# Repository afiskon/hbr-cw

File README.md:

# HBR/CW

**Update**: The project has some issues with spurious signals. This problem was addressed in [HBR/3B](https://github.com/afiskon/hbr-3b) and [HBR/8B](https://github.com/afiskon/hbr-8b).

All HF bands QRP CW transceiver

* Covers 80, 40, 30, 20, 17, 15, 12 and 10 meter bands
* IF-derived AGC
* Supports RIT, XIT and SHIFT
* 10-30 WPM Elekey-B type keyer + straight key mode
* Keyer settings are saved in EEPROM
* 5W class C power amplifier
* 9-pole low-pass filters
* HIGH SWR indicator
* Open-source firmware and hardware

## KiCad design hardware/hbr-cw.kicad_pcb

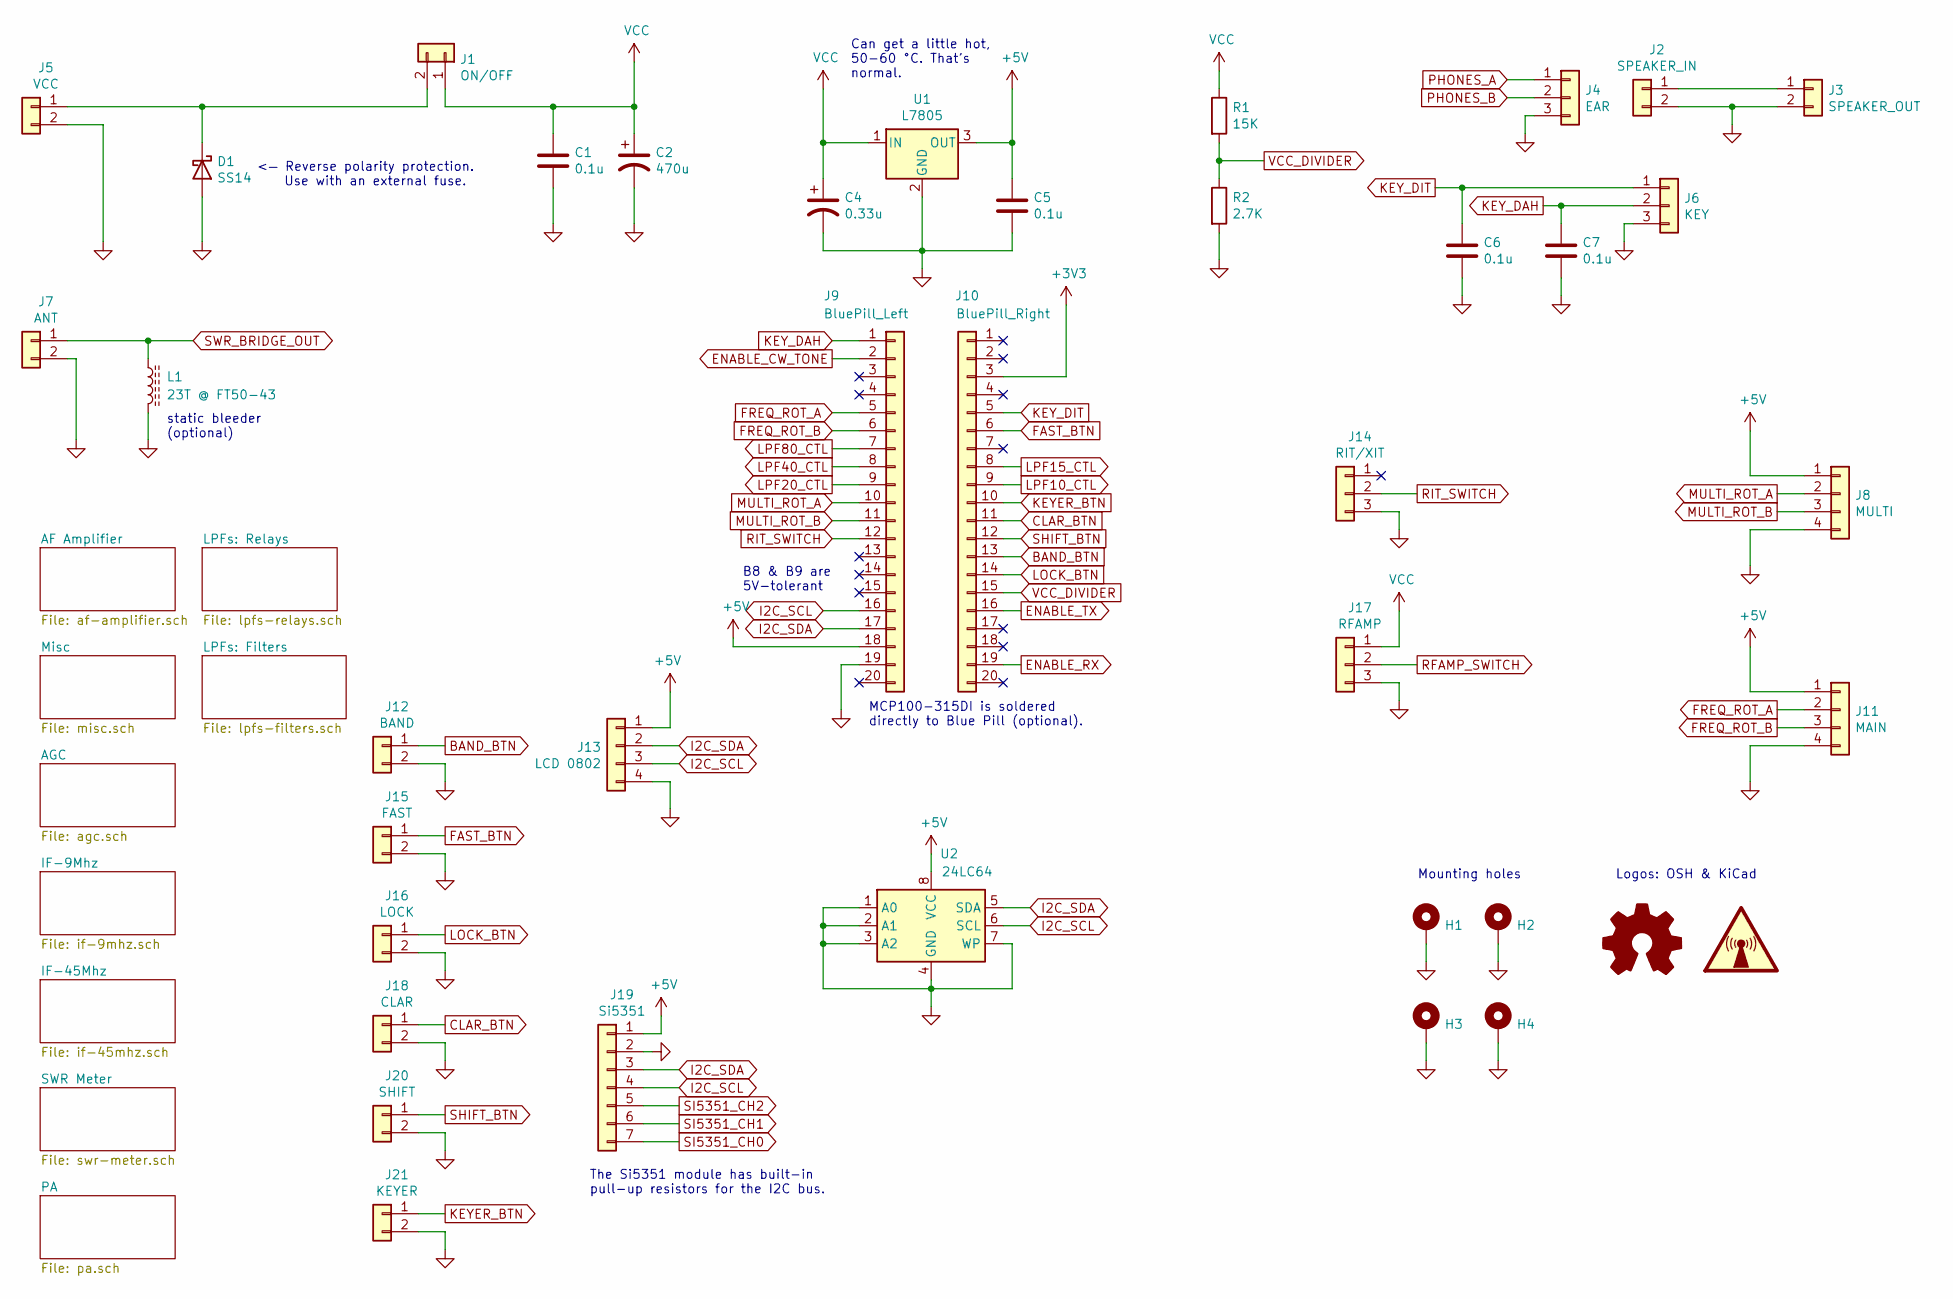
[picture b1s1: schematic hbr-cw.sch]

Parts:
C1, C5, C6, C7: 0.1u; C_0805_2012Metric_Pad1.15x1.40mm_HandSolder
C2: 470u; CP_Elec_10x10.5
C4: 0.33u; C_Radial_D5.0mm_H5.0mm_P2.00mm
D1: SS14; D_SMA_Handsoldering
H1, H2, H3, H4: MH; MountingHole_3.2mm_M3_Pad_Via
J1: ON/OFF; PinHeader_1x02_P2.54mm_Vertical
J2: SPEAKER_IN; PinHeader_1x02_P2.54mm_Vertical
J3: SPEAKER_OUT; PinHeader_1x02_P2.54mm_Vertical
J4: EAR; PinSocket_1x03_P2.54mm_Vertical
J5: VCC; PinHeader_1x02_P2.54mm_Vertical
J6: KEY; PinSocket_1x03_P2.54mm_Vertical
J7: ANT; PinHeader_1x02_P2.54mm_Vertical
J8: MULTI; PinHeader_1x04_P2.54mm_Vertical
J9: BluePill_Left; PinSocket_1x20_P2.54mm_Vertical
J10: BluePill_Right; PinSocket_1x20_P2.54mm_Vertical
J11: MAIN; PinHeader_1x04_P2.54mm_Vertical
J12: BAND; PinHeader_1x02_P2.54mm_Vertical
J13: LCD 0802; PinHeader_1x04_P2.54mm_Vertical
J14: RIT/XIT; PinSocket_1x03_P2.54mm_Vertical
J15: FAST; PinHeader_1x02_P2.54mm_Vertical
J16: LOCK; PinHeader_1x02_P2.54mm_Vertical
J17: RFAMP; PinSocket_1x03_P2.54mm_Vertical
J18: CLAR; PinHeader_1x02_P2.54mm_Vertical
J19: Si5351; PinHeader_1x07_P2.54mm_Vertical
J20: SHIFT; PinHeader_1x02_P2.54mm_Vertical
J21: KEYER; PinHeader_1x02_P2.54mm_Vertical
L1: 23T @ FT50-43; L_Toroid_Vertical_L13.0mm_W6.5mm_P5.60mm
R1: 15K; R_0805_2012Metric_Pad1.15x1.40mm_HandSolder
R2: 2.7K; R_0805_2012Metric_Pad1.15x1.40mm_HandSolder
SYM1: Logo_Open_Hardware_Small; OSHW-Logo2_9.8x8mm_SilkScreen
SYM2: SYM_Radio_Waves_Large; KiCad-Logo_5mm_SilkScreen
U1: L7805; TO-263-2
U2: 24LC64; SO-8_5.3x6.2mm_P1.27mm

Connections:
+3V3: J10.3
+5V: C5.1, J8.1, J9.18, J11.1, J13.1, J19.1, U1.3 (OUT), U2.8 (VCC); also elsewhere on the board
BAND_BTN: J10.13, J12.1
CLAR_BTN: J10.11, J18.1
ENABLE_CW_TONE: J9.2; also elsewhere on the board
ENABLE_RX: J10.19; also elsewhere on the board
ENABLE_TX: J10.16; also elsewhere on the board
FAST_BTN: J10.6, J15.1
FREQ_ROT_A: J9.5, J11.2
FREQ_ROT_B: J9.6, J11.3
GND: C1.2, C2.2, C4.2, C5.2, C6.2, C7.2, D1.2 (A), H1.1, H2.1, H3.1, H4.1, J2.2, J3.2, J4.3, J5.2, J6.3, J7.2, J8.4, J9.19, J11.4, J12.2, J13.4, J14.3, J15.2, J16.2, J17.3, J18.2, J19.2, J20.2, J21.2, L1.2, R2.2, U1.2 (GND), U2.1 (A0), U2.2 (A1), U2.3 (A2), U2.4 (GND), U2.7 (WP); also elsewhere on the board
I2C_SCL: J9.16, J13.3, J19.4, U2.6 (SCL); also elsewhere on the board
I2C_SDA: J9.17, J13.2, J19.3, U2.5 (SDA); also elsewhere on the board
KEYER_BTN: J10.10, J21.1
KEY_DAH: C7.1, J6.2, J9.1
KEY_DIT: C6.1, J6.1, J10.5
LOCK_BTN: J10.14, J16.1
LPF10_CTL: J10.9; also elsewhere on the board
LPF15_CTL: J10.8; also elsewhere on the board
LPF20_CTL: J9.9; also elsewhere on the board
LPF40_CTL: J9.8; also elsewhere on the board
LPF80_CTL: J9.7; also elsewhere on the board
MULTI_ROT_A: J8.2, J9.10
MULTI_ROT_B: J8.3, J9.11
unnamed: D1.1 (K), J1.2, J5.1
unnamed: J2.1, J3.1
PHONES_A: J4.1; also elsewhere on the board
PHONES_B: J4.2; also elsewhere on the board
RFAMP_SWITCH: J17.2; also elsewhere on the board
RIT_SWITCH: J9.12, J14.2
SHIFT_BTN: J10.12, J20.1
SI5351_CH0: J19.7; also elsewhere on the board
SI5351_CH1: J19.6; also elsewhere on the board
SI5351_CH2: J19.5; also elsewhere on the board
SWR_BRIDGE_OUT: J7.1, L1.1; also elsewhere on the board
VCC: C1.1, C2.1, C4.1, J1.1, J17.1, R1.1, U1.1 (IN); also elsewhere on the board
VCC_DIVIDER: J10.15, R1.2, R2.1

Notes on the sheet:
<— Reverse polarity protection. Use with an external fuse.
The Si5351 module has built-in pull-up resistors for the I2C bus.
static bleeder (optional)
B8 & B9 are 5V-tolerant
MCP100-315DI is soldered directly to Blue Pill (optional).
Mounting holes
Logos: OSH & KiCad
Can get a little hot, 50-60 °C. That’s normal.

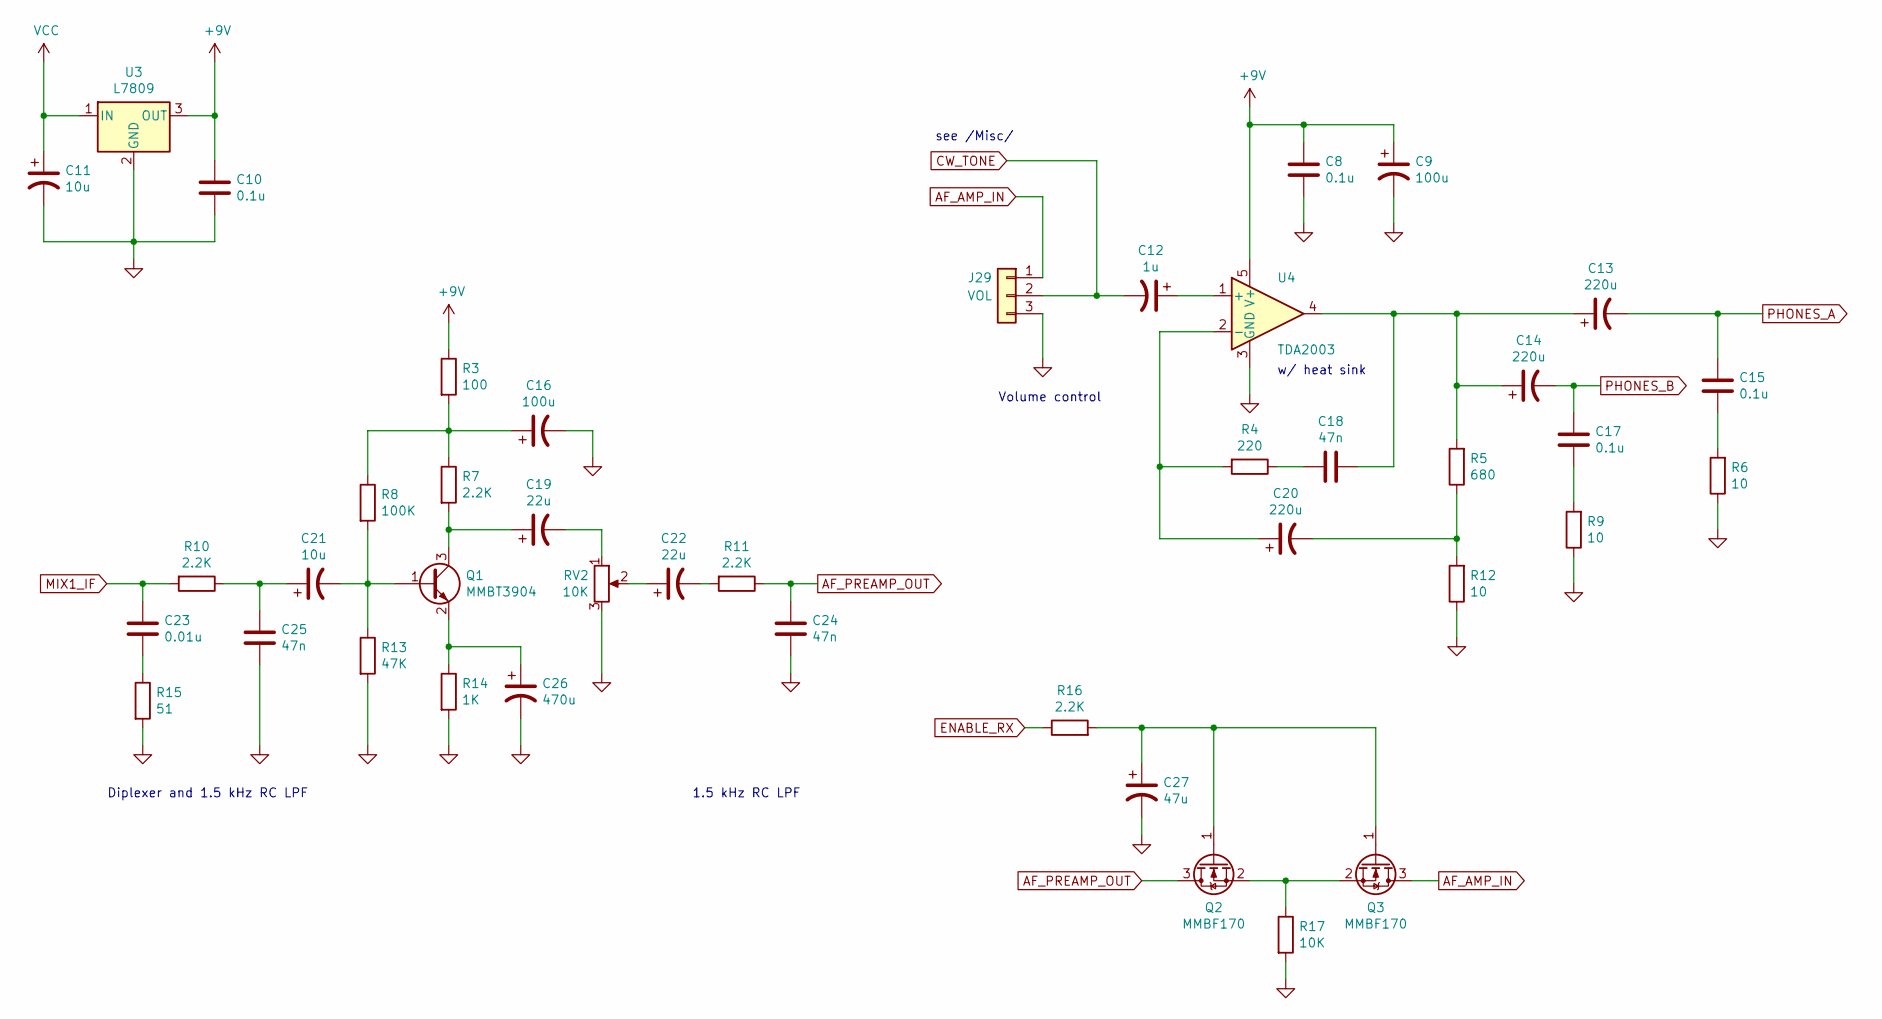
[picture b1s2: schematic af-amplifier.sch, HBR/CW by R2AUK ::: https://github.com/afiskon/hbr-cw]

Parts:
C8, C10, C15, C17: 0.1u; C_0805_2012Metric_Pad1.15x1.40mm_HandSolder
C9, C16: 100u; CP_Elec_6.3x7.7
C11, C21: 10u; CP_Elec_4x5.4
C12: 1u; CP_Elec_4x5.4
C13, C14, C20: 220u; CP_Elec_8x10.5
C18, C24, C25: 47n; C_0805_2012Metric_Pad1.15x1.40mm_HandSolder
C19, C22: 22u; CP_Elec_5x5.4
C23: 0.01u; C_0805_2012Metric_Pad1.15x1.40mm_HandSolder
C26: 470u; CP_Elec_10x10.5
C27: 47u; CP_Elec_6.3x5.8
J29: VOL; PinSocket_1x03_P2.54mm_Vertical
Q1: MMBT3904; SOT-23
Q2, Q3: MMBF170; SOT-23
R3: 100; R_0805_2012Metric_Pad1.15x1.40mm_HandSolder
R4: 220; R_0805_2012Metric_Pad1.15x1.40mm_HandSolder
R5: 680; R_0805_2012Metric_Pad1.15x1.40mm_HandSolder
R6, R9, R12: 10; R_0805_2012Metric_Pad1.15x1.40mm_HandSolder
R7, R10, R11, R16: 2.2K; R_0805_2012Metric_Pad1.15x1.40mm_HandSolder
R8: 100K; R_0805_2012Metric_Pad1.15x1.40mm_HandSolder
R13: 47K; R_0805_2012Metric_Pad1.15x1.40mm_HandSolder
R14: 1K; R_0805_2012Metric_Pad1.15x1.40mm_HandSolder
R15: 51; R_0805_2012Metric_Pad1.15x1.40mm_HandSolder
R17: 10K; R_0805_2012Metric_Pad1.15x1.40mm_HandSolder
RV2: 10K; Potentiometer_Bourns_3296W_Vertical
U3: L7809; TO-263-2
U4: TDA2003; TO-220-5_P3.4x3.7mm_StaggerOdd_Lead3.8mm_Vertical

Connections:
+9V: C8.1, C9.1, C10.1, R3.1, U3.3 (OUT), U4.5 (V+); also elsewhere on the board
AF_AMP_IN: J29.1, Q3.3 (D)
AF_PREAMP_OUT: C24.1, Q2.3 (D), R11.1
CW_TONE: C12.2, J29.2; also elsewhere on the board
ENABLE_RX: R16.1; also elsewhere on the board
GND: C8.2, C9.2, C10.2, C11.2, C16.2, C24.2, C25.2, C26.2, C27.2, J29.3, R6.1, R9.1, R12.1, R13.2, R14.2, R15.2, R17.2, RV2.3, U3.2 (GND), U4.3 (GND); also elsewhere on the board
MIX1_IF: C23.1, R10.2; also elsewhere on the board
unnamed: C12.1, U4.1 (+)
unnamed: C13.1, C14.1, C18.1, R5.2, U4.4
unnamed: C15.2, R6.2
unnamed: C16.1, R3.2, R7.1, R8.1
unnamed: C17.2, R9.2
unnamed: C18.2, R4.1
unnamed: C19.1, Q1.3 (C), R7.2
unnamed: C19.2, RV2.1
unnamed: C20.1, R4.2, U4.2 (-)
unnamed: C20.2, R5.1, R12.2
unnamed: C21.1, C25.1, R10.1
unnamed: C21.2, Q1.1 (B), R8.2, R13.1
unnamed: C22.1, RV2.2
unnamed: C22.2, R11.2
unnamed: C23.2, R15.1
unnamed: C26.1, Q1.2 (E), R14.1
unnamed: C27.1, Q2.1 (G), Q3.1 (G), R16.2
unnamed: Q2.2 (S), Q3.2 (S), R17.1
PHONES_A: C13.2, C15.1; also elsewhere on the board
PHONES_B: C14.2, C17.1; also elsewhere on the board
VCC: C11.1, U3.1 (IN); also elsewhere on the board

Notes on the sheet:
Volume control
w/ heat sink
see /Misc/
Diplexer and 1.5 kHz RC LPF
1.5 kHz RC LPF

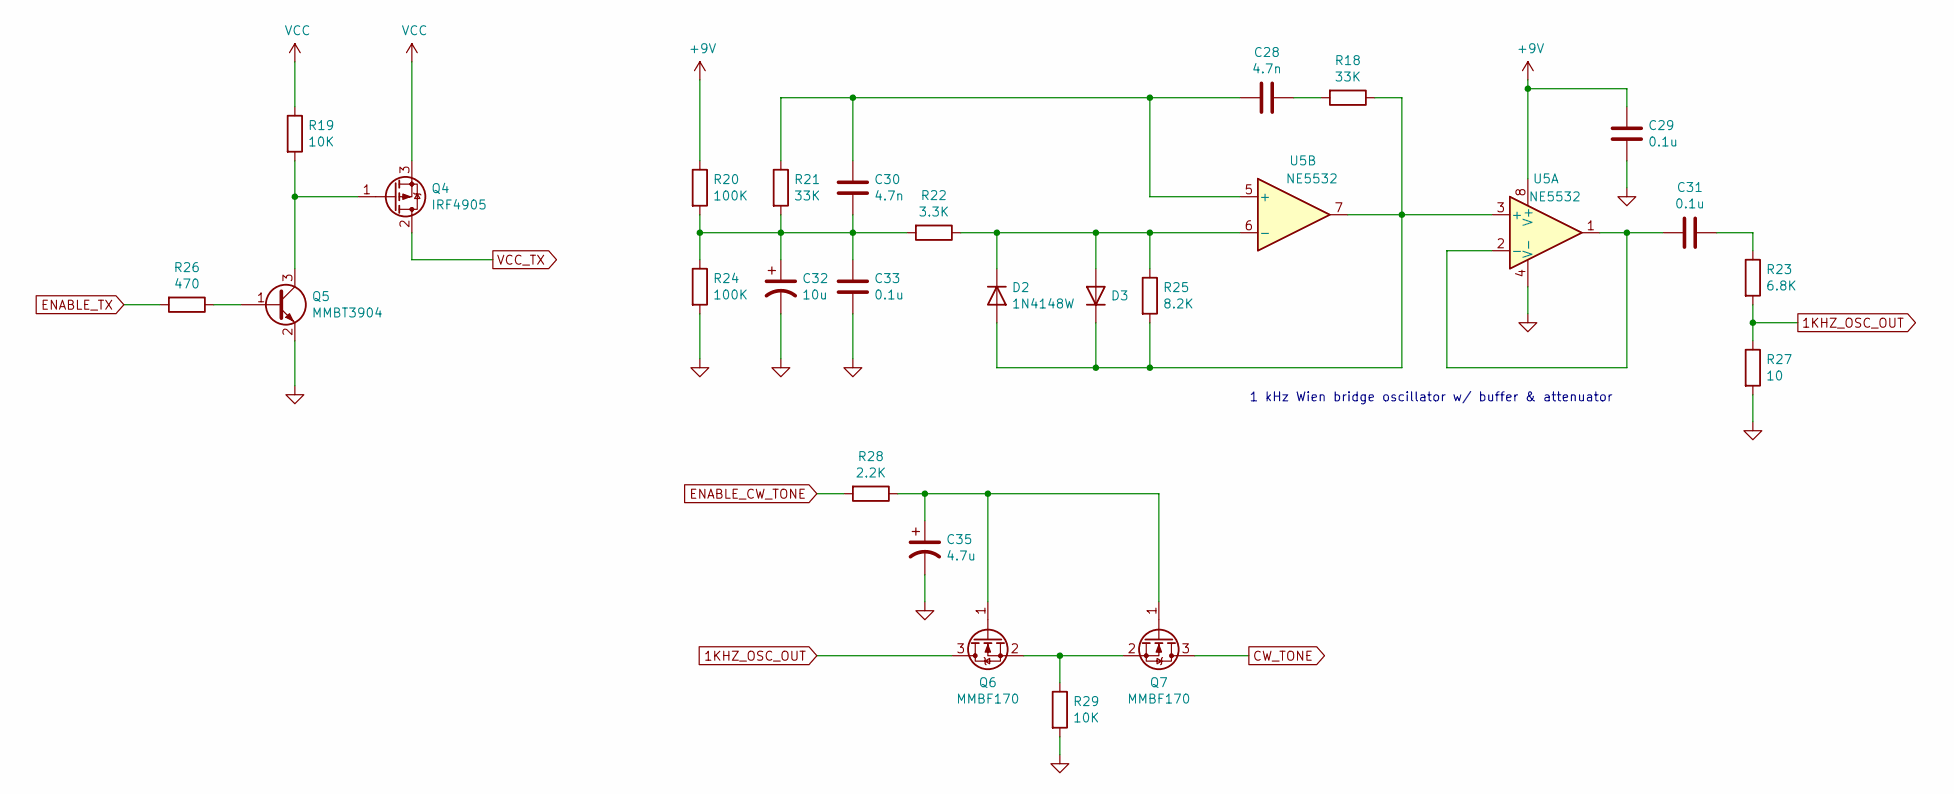
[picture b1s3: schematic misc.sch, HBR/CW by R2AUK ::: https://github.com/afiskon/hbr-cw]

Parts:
C28, C30: 4.7n; C_0805_2012Metric_Pad1.15x1.40mm_HandSolder
C29, C31, C33: 0.1u; C_0805_2012Metric_Pad1.15x1.40mm_HandSolder
C32: 10u; CP_Elec_4x5.4
C35: 4.7u; CP_Elec_4x5.4
D2, D3: 1N4148W; D_SOD-123
Q4: IRF4905; TO-220-3_Vertical
Q5: MMBT3904; SOT-23
Q6, Q7: MMBF170; SOT-23
R18, R21: 33K; R_0805_2012Metric_Pad1.15x1.40mm_HandSolder
R19, R29: 10K; R_0805_2012Metric_Pad1.15x1.40mm_HandSolder
R20, R24: 100K; R_0805_2012Metric_Pad1.15x1.40mm_HandSolder
R22: 3.3K; R_0805_2012Metric_Pad1.15x1.40mm_HandSolder
R23: 6.8K; R_0805_2012Metric_Pad1.15x1.40mm_HandSolder
R25: 8.2K; R_0805_2012Metric_Pad1.15x1.40mm_HandSolder
R26: 470; R_0805_2012Metric_Pad1.15x1.40mm_HandSolder
R27: 10; R_0805_2012Metric_Pad1.15x1.40mm_HandSolder
R28: 2.2K; R_0805_2012Metric_Pad1.15x1.40mm_HandSolder
U5: NE5532; SOIC-8_5.23x5.23mm_P1.27mm

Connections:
1KHZ_OSC_OUT: Q6.3 (D), R23.2, R27.1
+9V: C29.2, R20.1, U5.8 (V+); also elsewhere on the board
CW_TONE: Q7.3 (D); also elsewhere on the board
ENABLE_CW_TONE: R28.2; also elsewhere on the board
ENABLE_TX: R26.2; also elsewhere on the board
GND: C29.1, C32.2, C33.2, C35.2, Q5.2 (E), R24.2, R27.2, R29.2, U5.4 (V-); also elsewhere on the board
unnamed: C28.1, R18.2
unnamed: C28.2, C30.1, R21.1, U5.5 (+)
unnamed: C30.2, C32.1, C33.1, R20.2, R21.2, R22.2, R24.1
unnamed: C31.1, R23.1
unnamed: C31.2, U5.1, U5.2 (-)
unnamed: C35.1, Q6.1 (G), Q7.1 (G), R28.1
unnamed: D2.1 (K), D3.2 (A), R22.1, R25.1, U5.6 (-)
unnamed: D2.2 (A), D3.1 (K), R18.1, R25.2, U5.3 (+), U5.7
unnamed: Q4.1 (G), Q5.3 (C), R19.2
unnamed: Q5.1 (B), R26.1
unnamed: Q6.2 (S), Q7.2 (S), R29.1
VCC: Q4.3 (S), R19.1; also elsewhere on the board
VCC_TX: Q4.2 (D); also elsewhere on the board

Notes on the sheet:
1 kHz Wien bridge oscillator w/ buffer & attenuator

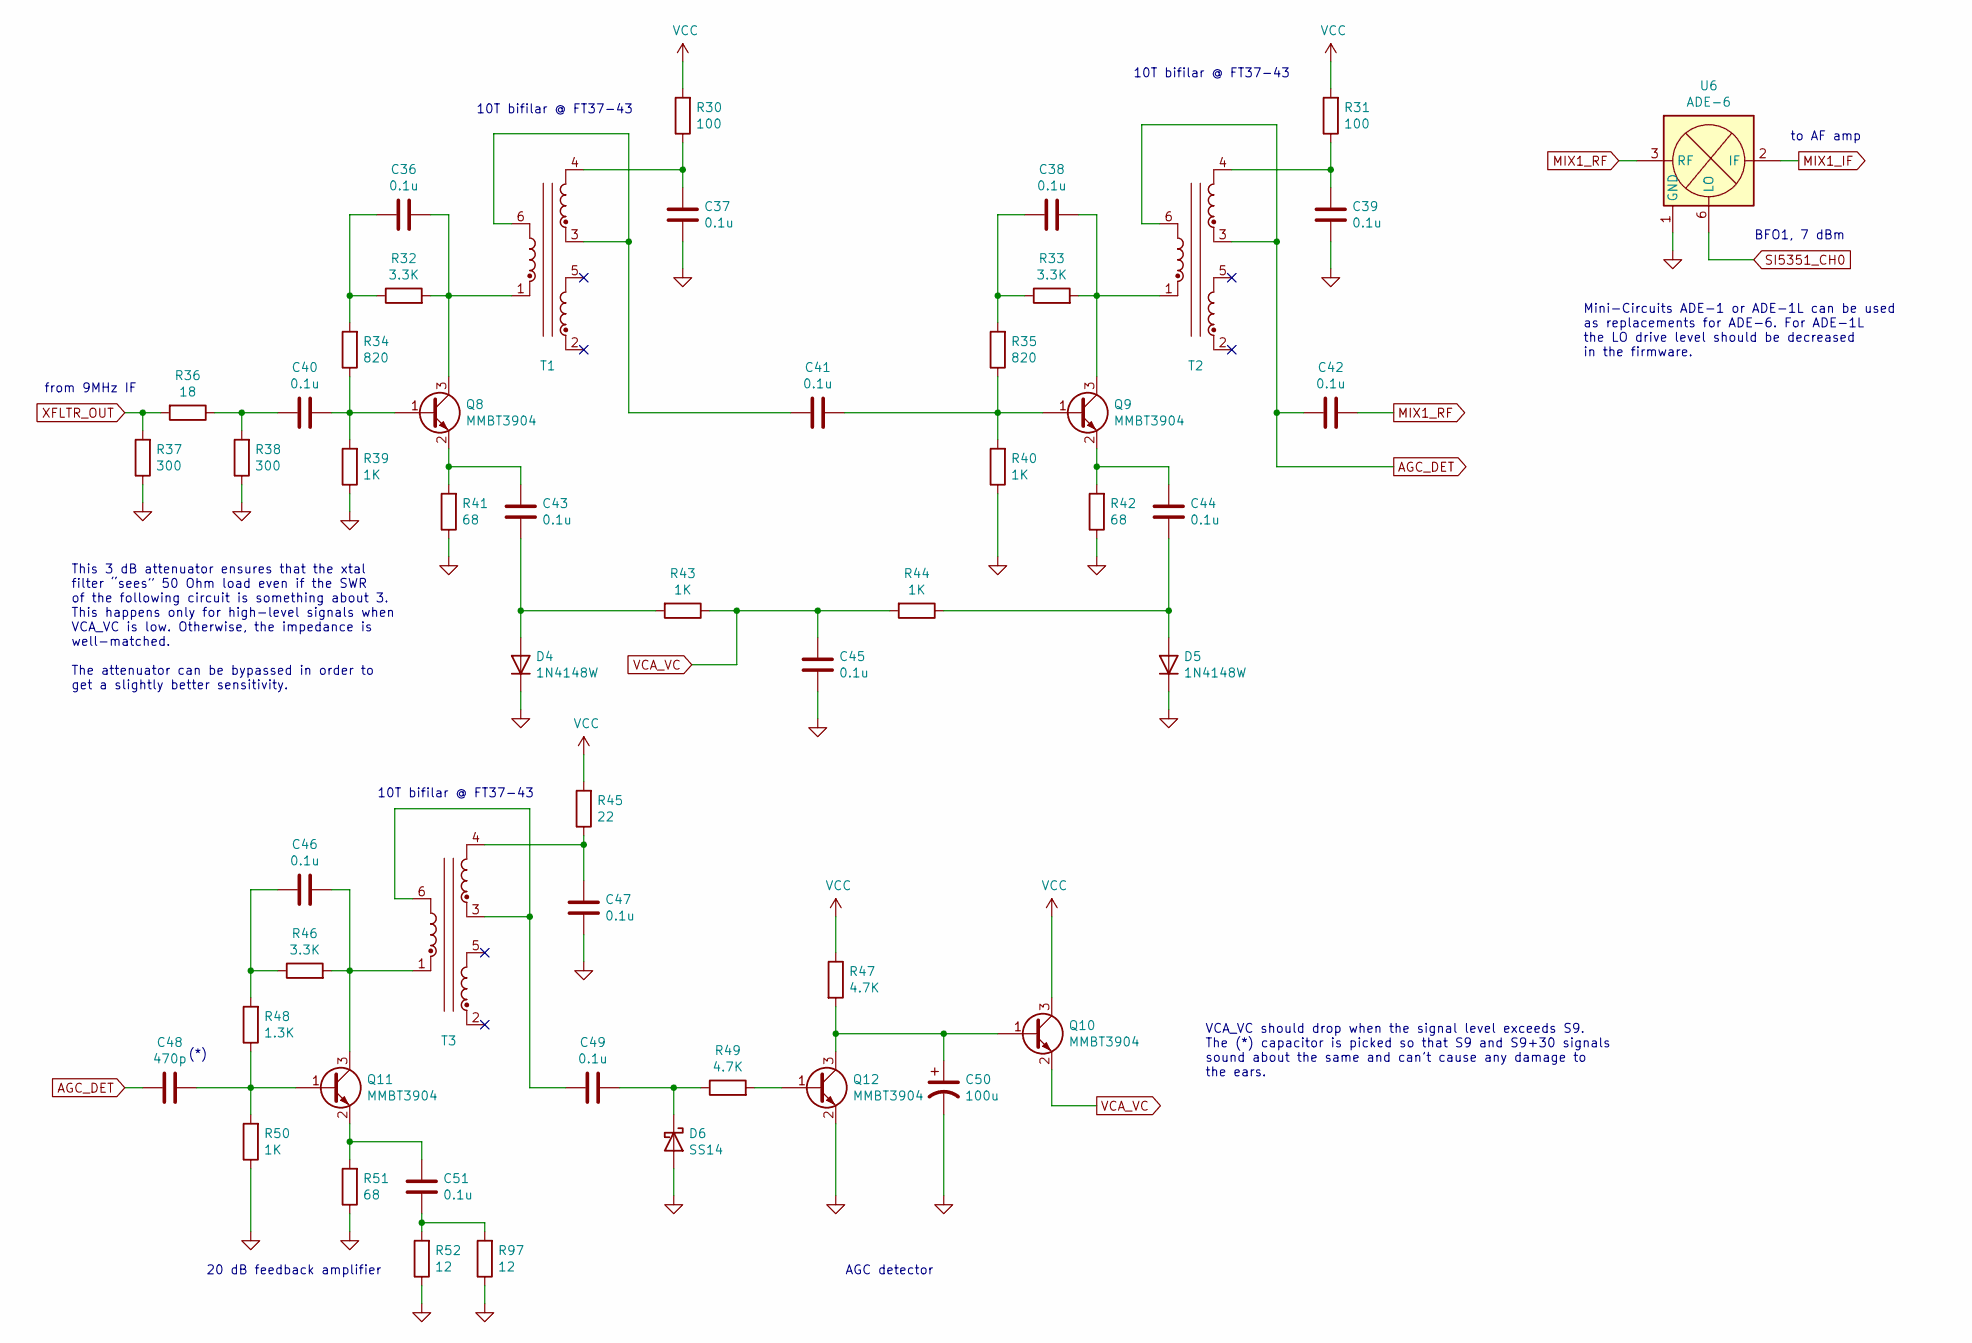
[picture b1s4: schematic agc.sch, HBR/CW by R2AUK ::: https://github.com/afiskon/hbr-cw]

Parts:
C36, C37, C38, C39, C40, C41, C42, C43, C44, C45, C46, C47, C49, C51: 0.1u; C_0805_2012Metric_Pad1.15x1.40mm_HandSolder
C48: 470p; C_0805_2012Metric_Pad1.15x1.40mm_HandSolder
C50: 100u; CP_Elec_6.3x7.7
D4, D5: 1N4148W; D_SOD-123
D6: SS14; D_SMA_Handsoldering
Q8, Q9, Q10, Q11, Q12: MMBT3904; SOT-23
R30, R31: 100; R_0805_2012Metric_Pad1.15x1.40mm_HandSolder
R32, R33, R46: 3.3K; R_0805_2012Metric_Pad1.15x1.40mm_HandSolder
R34, R35: 820; R_0805_2012Metric_Pad1.15x1.40mm_HandSolder
R36: 18; R_0805_2012Metric_Pad1.15x1.40mm_HandSolder
R37, R38: 300; R_0805_2012Metric_Pad1.15x1.40mm_HandSolder
R39, R40, R43, R44, R50: 1K; R_0805_2012Metric_Pad1.15x1.40mm_HandSolder
R41, R42, R51: 68; R_0805_2012Metric_Pad1.15x1.40mm_HandSolder
R45: 22; R_0805_2012Metric_Pad1.15x1.40mm_HandSolder
R47, R49: 4.7K; R_0805_2012Metric_Pad1.15x1.40mm_HandSolder
R48: 1.3K; R_0805_2012Metric_Pad1.15x1.40mm_HandSolder
R52, R97: 12; R_0805_2012Metric_Pad1.15x1.40mm_HandSolder
T1, T2, T3: FT37-43; DIP-6_W7.62mm
U6: ADE-6; Mini-Circuits_CD542_LandPatternPL-052

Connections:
AGC_DET: C42.2, C48.2, T2.3, T2.6
GND: C37.1, C39.1, C45.1, C47.1, C50.2, D4.1 (K), D5.1 (K), D6.2 (A), Q12.2 (E), R37.1, R38.1, R39.1, R40.1, R41.1, R42.1, R50.1, R51.1, R52.1, R97.1, U6.1 (GND), U6.4 (GND), U6.5 (GND); also elsewhere on the board
MIX1_IF: U6.2 (IF); also elsewhere on the board
MIX1_RF: C42.1, U6.3 (RF)
unnamed: C36.1, Q8.3 (C), R32.2, T1.1
unnamed: C36.2, R32.1, R34.2
unnamed: C37.2, R30.1, T1.4
unnamed: C38.1, Q9.3 (C), R33.2, T2.1
unnamed: C38.2, R33.1, R35.2
unnamed: C39.2, R31.1, T2.4
unnamed: C40.1, Q8.1 (B), R34.1, R39.2
unnamed: C40.2, R36.1, R38.2
unnamed: C41.1, Q9.1 (B), R35.1, R40.2
unnamed: C41.2, T1.3, T1.6
unnamed: C43.1, D4.2 (A), R43.2
unnamed: C43.2, Q8.2 (E), R41.2
unnamed: C44.1, D5.2 (A), R44.1
unnamed: C44.2, Q9.2 (E), R42.2
unnamed: C46.1, Q11.3 (C), R46.2, T3.1
unnamed: C46.2, R46.1, R48.2
unnamed: C47.2, R45.1, T3.4
unnamed: C48.1, Q11.1 (B), R48.1, R50.2
unnamed: C49.1, D6.1 (K), R49.1
unnamed: C49.2, T3.3, T3.6
unnamed: C50.1, Q10.1 (B), Q12.3 (C), R47.2
unnamed: C51.1, R52.2, R97.2
unnamed: C51.2, Q11.2 (E), R51.2
unnamed: Q12.1 (B), R49.2
SI5351_CH0: U6.6 (LO); also elsewhere on the board
VCA_VC: C45.2, Q10.2 (E), R43.1, R44.2
VCC: Q10.3 (C), R30.2, R31.2, R45.2, R47.1; also elsewhere on the board
XFLTR_OUT: R36.2, R37.2; also elsewhere on the board

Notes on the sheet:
10T bifilar @ FT37-43
BFO1, 7 dBm
20 dB feedback amplifier
VCA_VC should drop when the signal level exceeds S9. The (*) capacitor is picked so that S9 and S9+30 signals sound about the same and can’t cause any damage to the ears.
AGC detector
(*)
This 3 dB attenuator ensures that the xtal filter “sees” 50 Ohm load even if the SWR of the following circuit is something about 3. This happens only for high-level signals when VCA_VC is low. Otherwise, the impedance is well-matched. The attenuator can be bypassed in order to get a slightly better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
from 9MHz IF
to AF amp
Mini-Circuits ADE-1 or ADE-1L can be used as replacements for ADE-6. For ADE-1L the LO drive level should be decreased in the firmware.

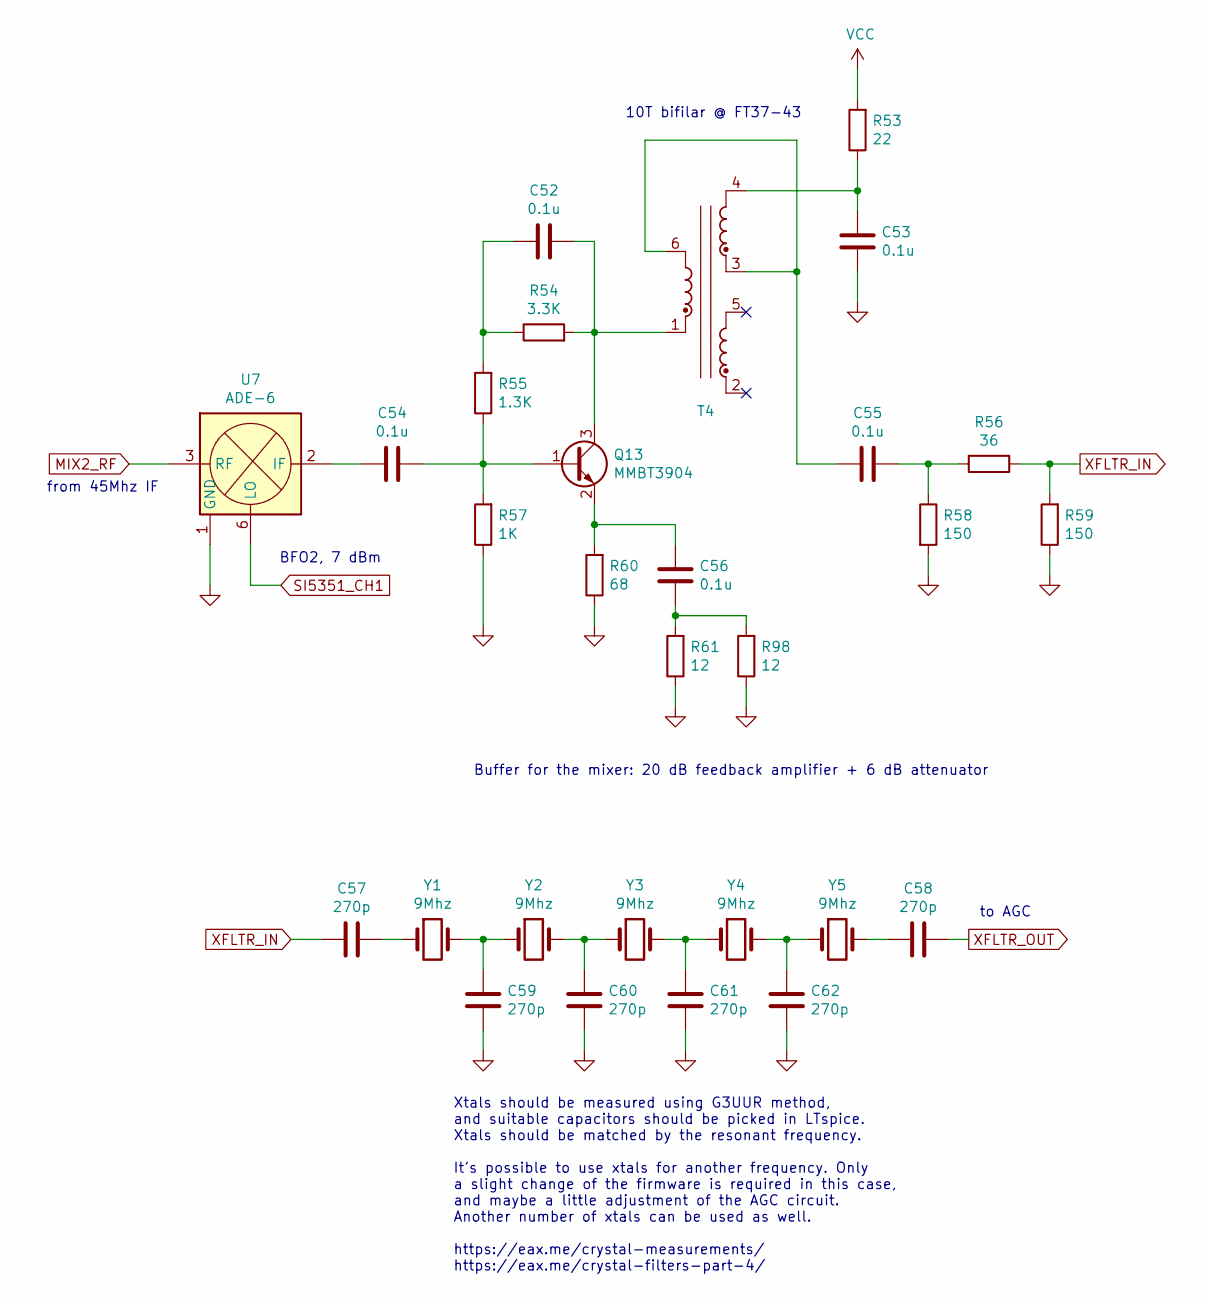
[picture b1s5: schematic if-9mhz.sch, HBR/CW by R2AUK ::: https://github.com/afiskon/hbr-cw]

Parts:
C52, C53, C54, C55, C56: 0.1u; C_0805_2012Metric_Pad1.15x1.40mm_HandSolder
C57, C58, C59, C60, C61, C62: 270p; C_0805_2012Metric_Pad1.15x1.40mm_HandSolder
Q13: MMBT3904; SOT-23
R53: 22; R_0805_2012Metric_Pad1.15x1.40mm_HandSolder
R54: 3.3K; R_0805_2012Metric_Pad1.15x1.40mm_HandSolder
R55: 1.3K; R_0805_2012Metric_Pad1.15x1.40mm_HandSolder
R56: 36; R_0805_2012Metric_Pad1.15x1.40mm_HandSolder
R57: 1K; R_0805_2012Metric_Pad1.15x1.40mm_HandSolder
R58, R59: 150; R_0805_2012Metric_Pad1.15x1.40mm_HandSolder
R60: 68; R_0805_2012Metric_Pad1.15x1.40mm_HandSolder
R61, R98: 12; R_0805_2012Metric_Pad1.15x1.40mm_HandSolder
T4: FT37-43; DIP-6_W7.62mm
U7: ADE-6; Mini-Circuits_CD542_LandPatternPL-052
Y1, Y2, Y3, Y4, Y5: 9Mhz; Crystal_HC49-U_Vertical

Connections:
GND: C53.1, C59.2, C60.2, C61.2, C62.2, R57.1, R58.2, R59.1, R60.1, R61.1, R98.1, U7.1 (GND), U7.4 (GND), U7.5 (GND); also elsewhere on the board
MIX2_RF: U7.3 (RF); also elsewhere on the board
unnamed: C52.1, Q13.3 (C), R54.2, T4.1
unnamed: C52.2, R54.1, R55.2
unnamed: C53.2, R53.1, T4.4
unnamed: C54.1, Q13.1 (B), R55.1, R57.2
unnamed: C54.2, U7.2 (IF)
unnamed: C55.1, R56.2, R58.1
unnamed: C55.2, T4.3, T4.6
unnamed: C56.1, R61.2, R98.2
unnamed: C56.2, Q13.2 (E), R60.2
unnamed: C57.1, Y1.1
unnamed: C58.2, Y5.2
unnamed: C59.1, Y1.2, Y2.1
unnamed: C60.1, Y2.2, Y3.1
unnamed: C61.1, Y3.2, Y4.1
unnamed: C62.1, Y4.2, Y5.1
SI5351_CH1: U7.6 (LO); also elsewhere on the board
VCC: R53.2; also elsewhere on the board
XFLTR_IN: C57.2, R56.1, R59.2
XFLTR_OUT: C58.1; also elsewhere on the board

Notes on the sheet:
10T bifilar @ FT37-43
Buffer for the mixer: 20 dB feedback amplifier + 6 dB attenuator
BFO2, 7 dBm
from 45Mhz IF
to AGC
Xtals should be measured using G3UUR method, and suitable capacitors should be picked in LTspice. Xtals should be matched by the resonant frequency. It’s possible to use xtals for another frequency. Only a slight change of the firmware is required in this case, and maybe a little adjustment of the 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

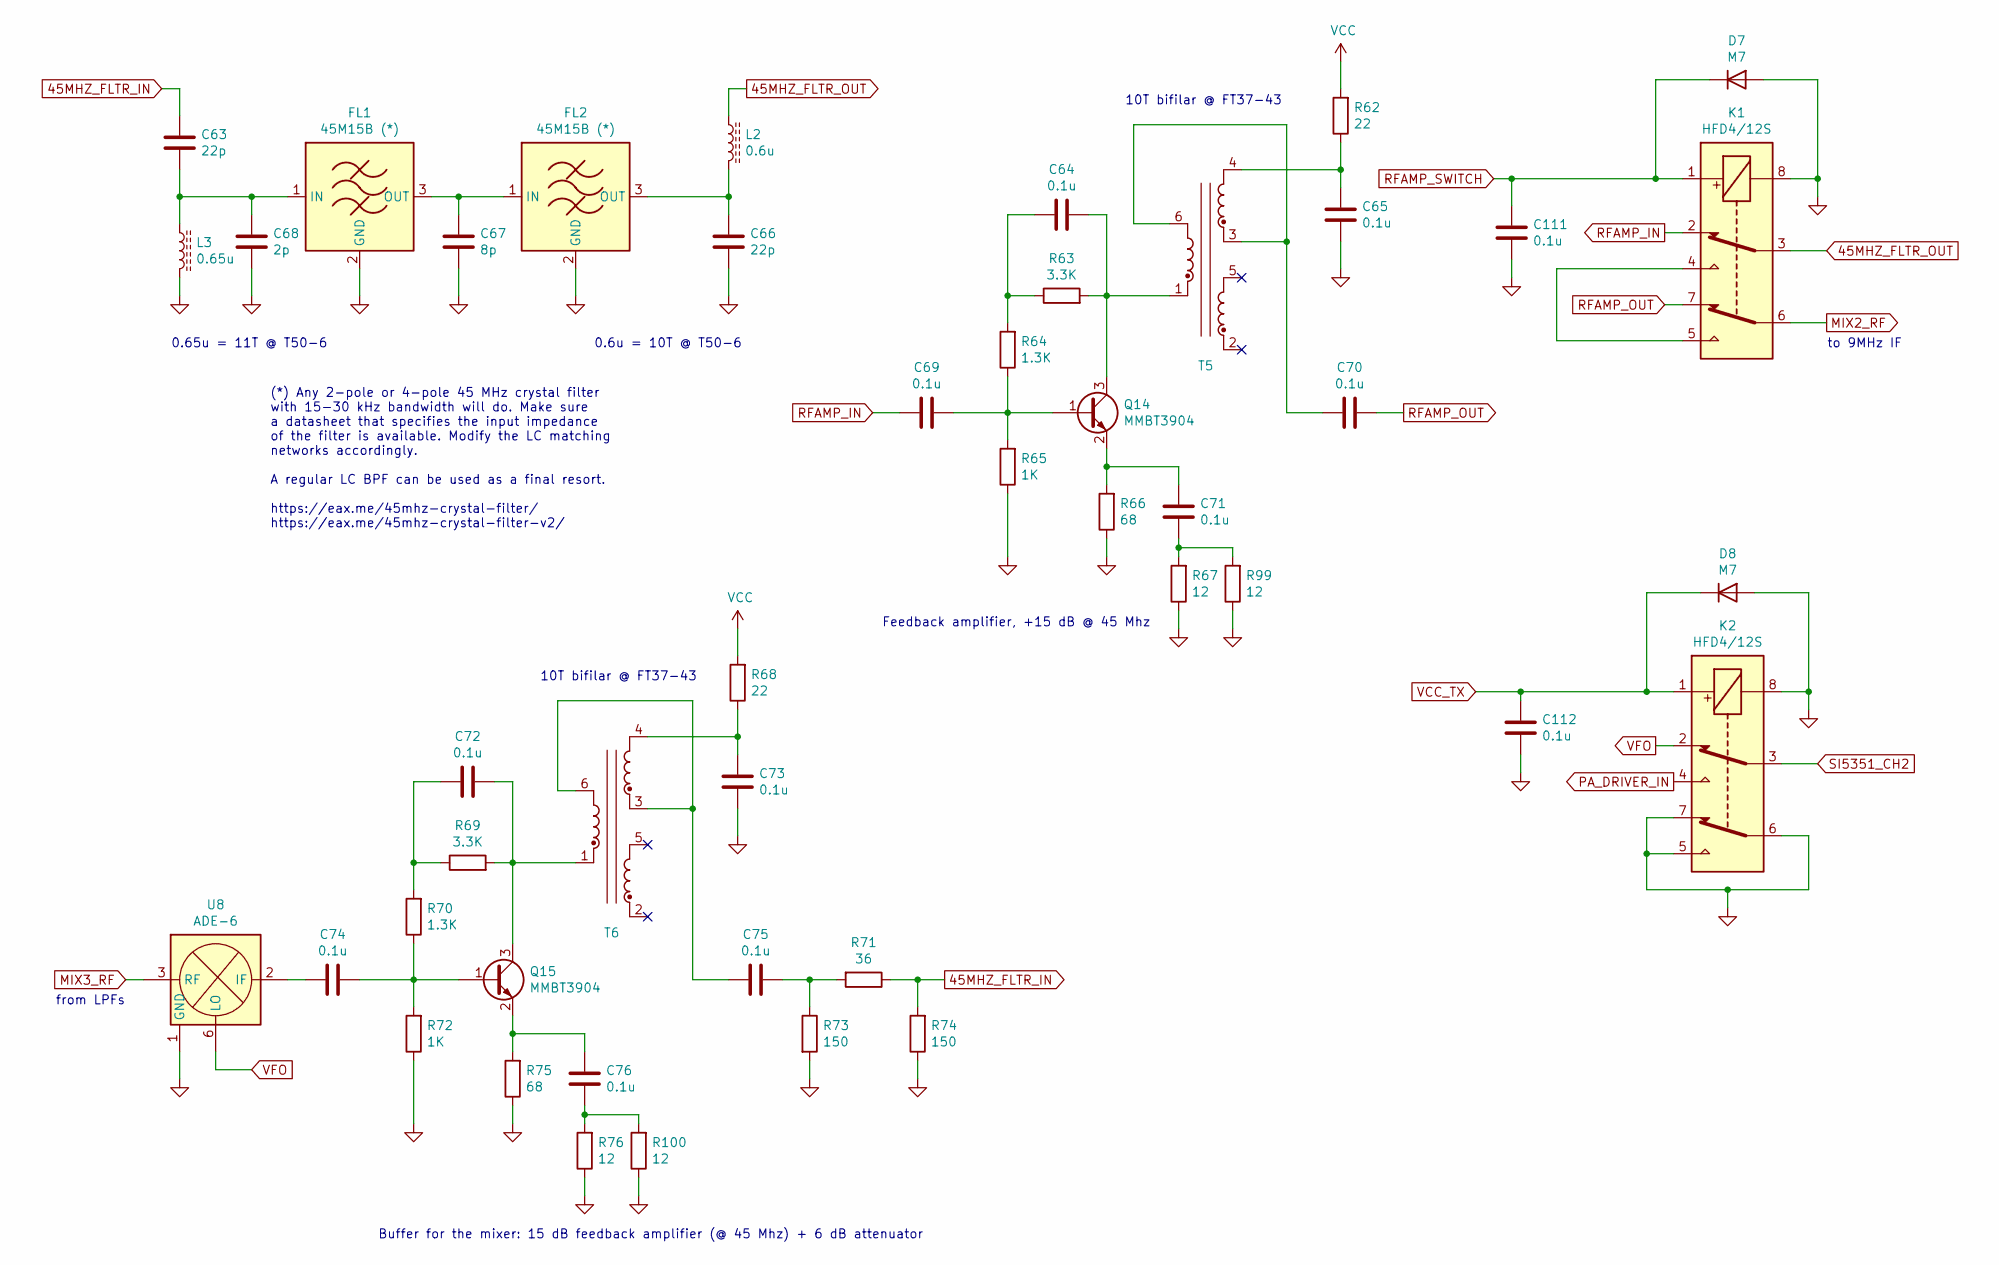
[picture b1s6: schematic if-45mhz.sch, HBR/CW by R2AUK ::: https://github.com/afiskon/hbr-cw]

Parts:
C63, C66: 22p; C_0805_2012Metric_Pad1.15x1.40mm_HandSolder
C64, C65, C69, C70, C71, C72, C73, C74, C75, C76, C111, C112: 0.1u; C_0805_2012Metric_Pad1.15x1.40mm_HandSolder
C67: 8p; C_0805_2012Metric_Pad1.15x1.40mm_HandSolder
C68: 2p; C_0805_2012Metric_Pad1.15x1.40mm_HandSolder
D7, D8: M7; D_SMA_Handsoldering
FL1, FL2: 45M15B (*); Resonator-3Pin_W7.0mm_H2.5mm
K1, K2: HFD4/12S; Relay_DPDT_Omron_G6K-2F-Y
L2: 0.6u; L_Toroid_Vertical_L13.0mm_W6.5mm_P5.60mm
L3: 0.65u; L_Toroid_Vertical_L13.0mm_W6.5mm_P5.60mm
Q14, Q15: MMBT3904; SOT-23
R62, R68: 22; R_0805_2012Metric_Pad1.15x1.40mm_HandSolder
R63, R69: 3.3K; R_0805_2012Metric_Pad1.15x1.40mm_HandSolder
R64, R70: 1.3K; R_0805_2012Metric_Pad1.15x1.40mm_HandSolder
R65, R72: 1K; R_0805_2012Metric_Pad1.15x1.40mm_HandSolder
R66, R75: 68; R_0805_2012Metric_Pad1.15x1.40mm_HandSolder
R67, R76, R99, R100: 12; R_0805_2012Metric_Pad1.15x1.40mm_HandSolder
R71: 36; R_0805_2012Metric_Pad1.15x1.40mm_HandSolder
R73, R74: 150; R_0805_2012Metric_Pad1.15x1.40mm_HandSolder
T5, T6: FT37-43; DIP-6_W7.62mm
U8: ADE-6; Mini-Circuits_CD542_LandPatternPL-052

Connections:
45MHZ_FLTR_IN: C63.1, R71.1, R74.2
45MHZ_FLTR_OUT: K1.3, L2.1
GND: C65.1, C66.1, C67.1, C68.1, C73.1, C111.2, C112.2, D7.2 (A), D8.2 (A), FL1.2 (GND), FL2.2 (GND), K1.8, K2.5, K2.6, K2.7, K2.8, L3.2, R65.1, R66.1, R67.1, R72.1, R73.2, R74.1, R75.1, R76.1, R99.1, R100.1, U8.1 (GND), U8.4 (GND), U8.5 (GND); also elsewhere on the board
MIX2_RF: K1.6; also elsewhere on the board
MIX3_RF: U8.3 (RF); also elsewhere on the board
unnamed: C63.2, C68.2, FL1.1 (IN), L3.1
unnamed: C64.1, Q14.3 (C), R63.2, T5.1
unnamed: C64.2, R63.1, R64.2
unnamed: C65.2, R62.1, T5.4
unnamed: C66.2, FL2.3 (OUT), L2.2
unnamed: C67.2, FL1.3 (OUT), FL2.1 (IN)
unnamed: C69.1, Q14.1 (B), R64.1, R65.2
unnamed: C70.2, T5.3, T5.6
unnamed: C71.1, R67.2, R99.2
unnamed: C71.2, Q14.2 (E), R66.2
unnamed: C72.1, Q15.3 (C), R69.2, T6.1
unnamed: C72.2, R69.1, R70.2
unnamed: C73.2, R68.1, T6.4
unnamed: C74.1, Q15.1 (B), R70.1, R72.2
unnamed: C74.2, U8.2 (IF)
unnamed: C75.1, R71.2, R73.1
unnamed: C75.2, T6.3, T6.6
unnamed: C76.1, R76.2, R100.2
unnamed: C76.2, Q15.2 (E), R75.2
unnamed: K1.4, K1.5
PA_DRIVER_IN: K2.4; also elsewhere on the board
RFAMP_IN: C69.2, K1.2
RFAMP_OUT: C70.1, K1.7
RFAMP_SWITCH: C111.1, D7.1 (K), K1.1; also elsewhere on the board
SI5351_CH2: K2.3; also elsewhere on the board
VCC: R62.2, R68.2; also elsewhere on the board
VCC_TX: C112.1, D8.1 (K), K2.1; also elsewhere on the board
VFO: K2.2, U8.6 (LO)

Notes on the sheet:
10T bifilar @ FT37-43
Feedback amplifier, +15 dB @ 45 Mhz
Buffer for the mixer: 15 dB feedback amplifier (@ 45 Mhz) + 6 dB attenuator
to 9MHz IF
from LPFs
0.6u = 10T @ T50-6
0.65u = 11T @ T50-6
(*) Any 2-pole or 4-pole 45 MHz crystal filter with 15-30 kHz bandwidth will do. Make sure a datasheet that specifies the input impedance of the filter is available. Modify the LC matching networks accordingly. A regular LC BPF can be used as a final resort. https://eax.me/45mhz-crystal-filter/ htt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
